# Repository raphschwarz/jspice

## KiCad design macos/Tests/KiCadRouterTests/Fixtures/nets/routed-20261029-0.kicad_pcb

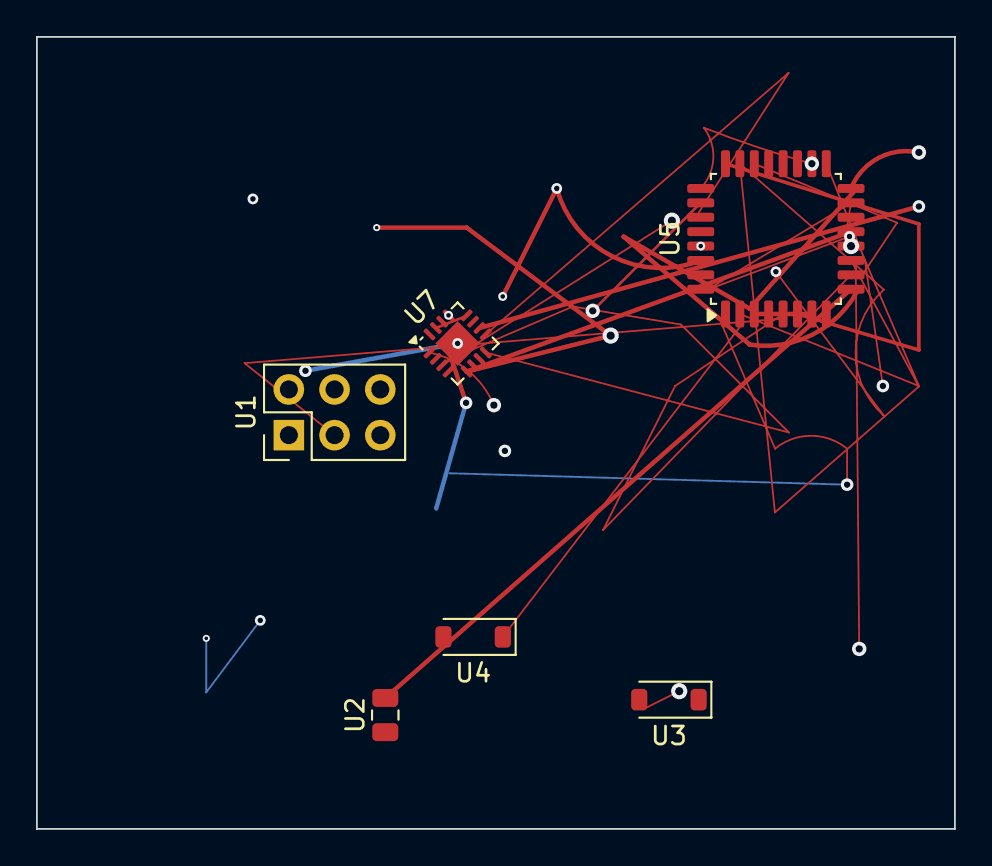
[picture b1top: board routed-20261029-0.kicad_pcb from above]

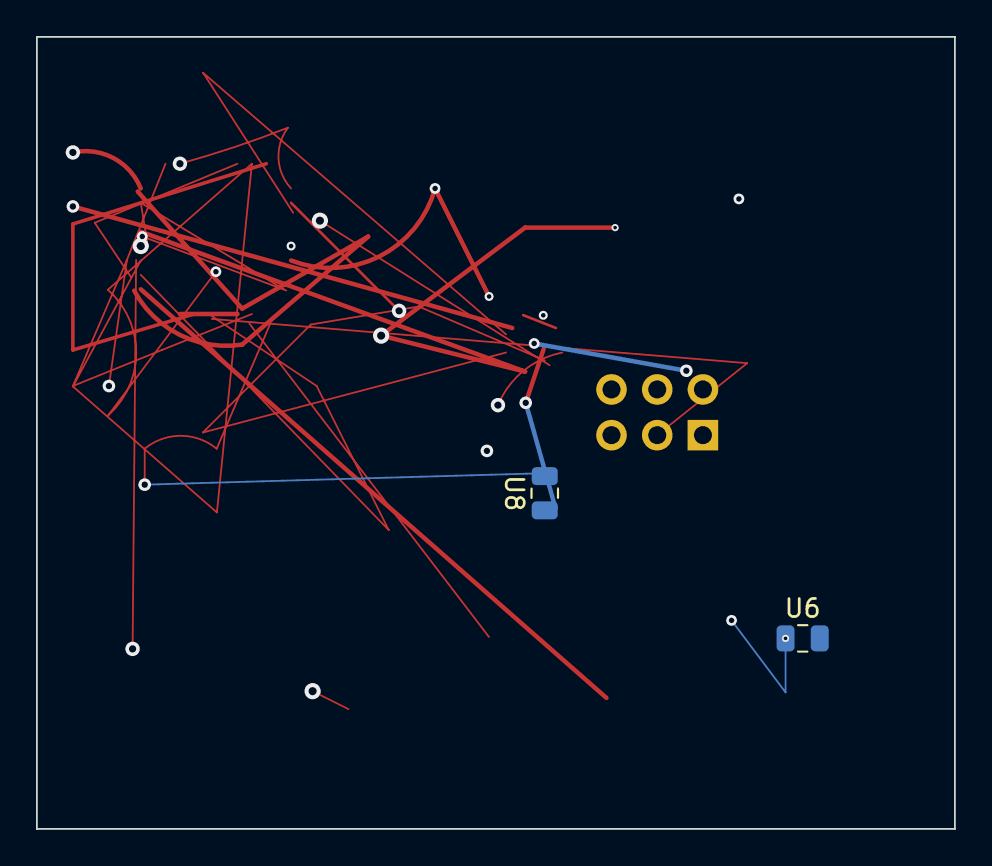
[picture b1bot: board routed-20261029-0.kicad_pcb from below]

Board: 6 copper layers, 51.0 x 44.0 mm, 8 parts (2 on the bottom side), 10 nets.

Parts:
U1: PinHeader_2x03_P2.54mm_Vertical
U2, U6, U8: C_0805_2012Metric
U3, U4: D_SOD-123
U5: LQFP-32_7x7mm_P0.8mm
U7: QFN-16-1EP_3x3mm_P0.5mm_EP1.75x1.75mm

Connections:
4k7: U5.3, U5.7, U5.30, U7.2, U7.16
+3V3: U1.1, U1.5, U5.12, U5.15, U5.32, U7.3, U7.8
/sub/CLK2: U5.6, U5.24, U5.31
/sub/clk: U5.26, U5.29, U7.12, U7.15
D12: U4.1, U5.2, U5.17, U5.18, U5.25
unnamed: U3.1, U5.1, U8.2
R1: U2.2, U5.9, U5.16, U7.10
R10: U3.2, U5.11, U5.23, U6.1, U7.1
SIG10: U1.3, U5.5, U5.10, U5.22, U5.27, U7.9
VCC: U5.13, U7.5, U7.13, U7.17, U8.1

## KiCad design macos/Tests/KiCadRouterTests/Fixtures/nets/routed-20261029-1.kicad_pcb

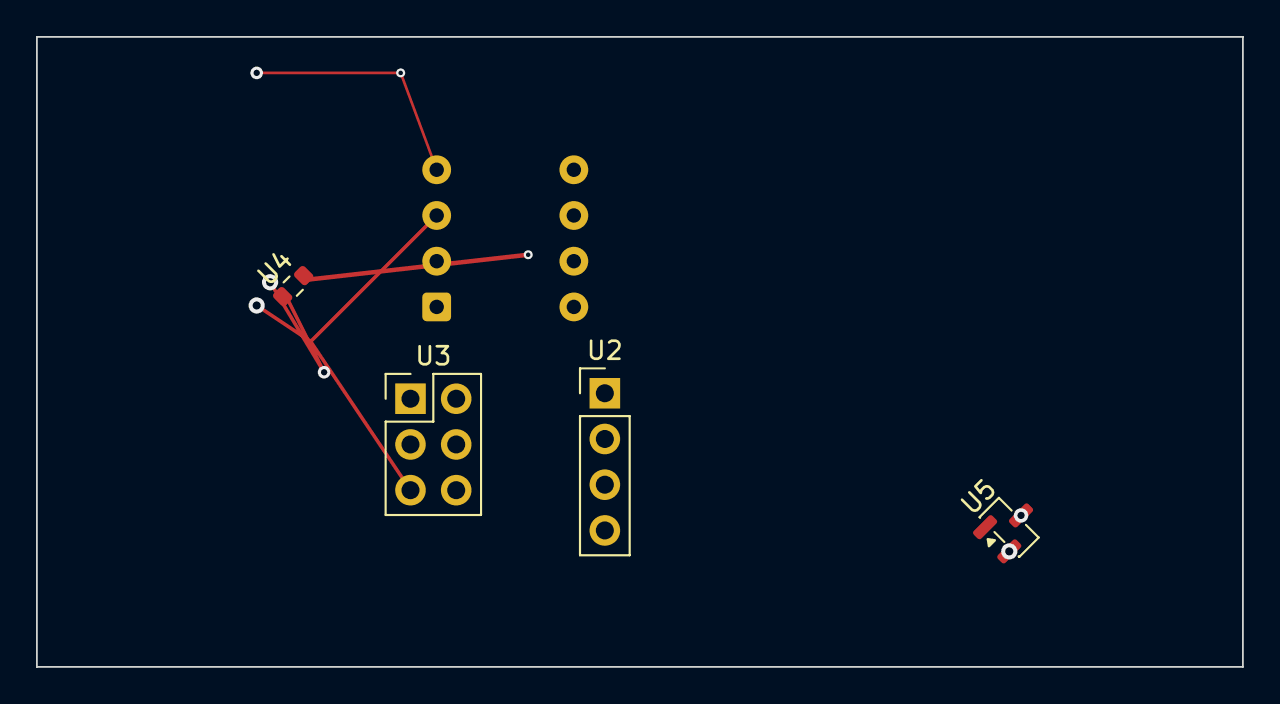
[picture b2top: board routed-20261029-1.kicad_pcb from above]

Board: 6 copper layers, 67.0 x 35.0 mm, 5 parts (1 on the bottom side), 4 nets.

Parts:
U1: DIP-8_W7.62mm
U2: PinHeader_1x04_P2.54mm_Vertical
U3: PinHeader_2x03_P2.54mm_Vertical
U4: R_0603_1608Metric
U5: SOT-23

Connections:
4K7_IN: U1.4, U1.7, U2.3
D12: U1.1, U1.8
GND: U1.3, U3.5, U5.3
VCC: U4.1, U5.2

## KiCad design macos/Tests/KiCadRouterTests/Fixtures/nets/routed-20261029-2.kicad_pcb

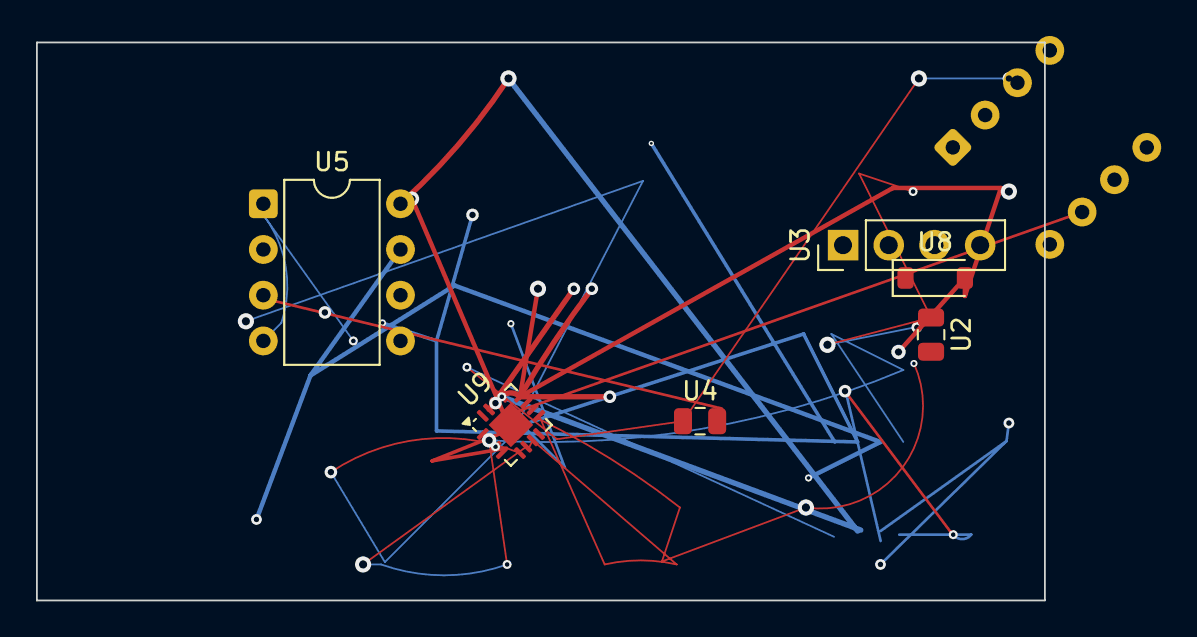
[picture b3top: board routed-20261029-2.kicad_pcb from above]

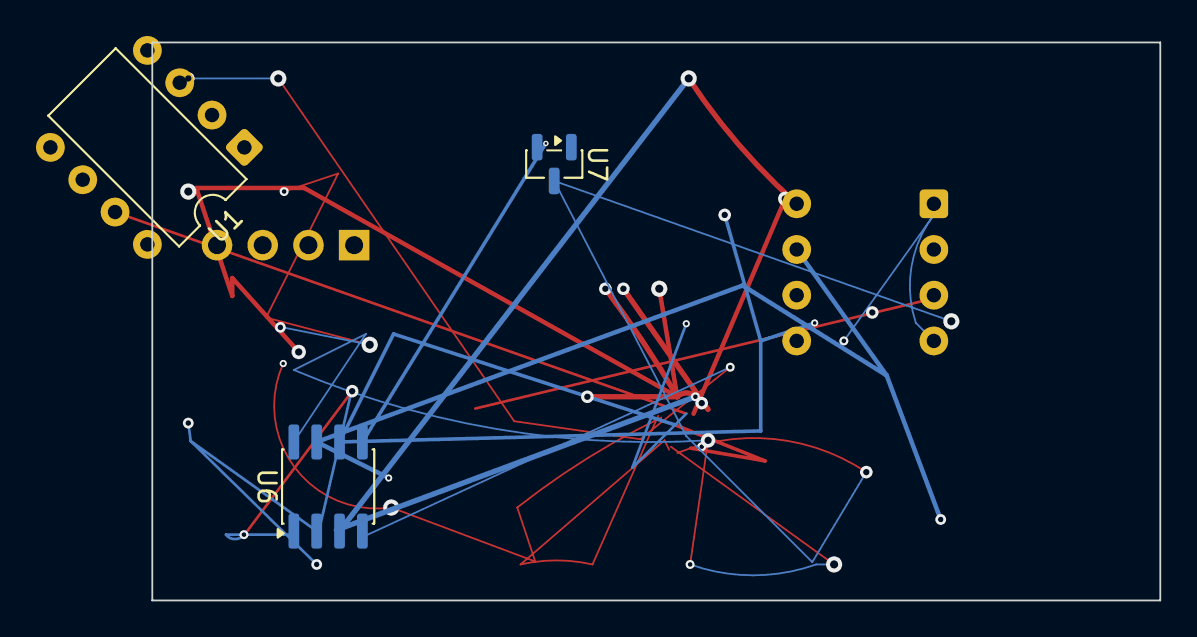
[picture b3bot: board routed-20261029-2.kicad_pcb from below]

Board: 4 copper layers, 56.0 x 31.0 mm, 9 parts (3 on the bottom side), 8 nets.

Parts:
U1, U5: DIP-8_W7.62mm
U2, U4: C_0805_2012Metric
U3: PinHeader_1x04_P2.54mm_Vertical
U6: SOIC-8_3.9x4.9mm_P1.27mm
U7: SOT-23
U8: D_SOD-123
U9: QFN-16-1EP_3x3mm_P0.5mm_EP1.75x1.75mm

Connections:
/sub/clk: U1.8, U5.5, U6.5, U6.6, U9.4, U9.16
D7: U1.7, U9.3
GND: U1.5, U4.1, U6.4, U6.8, U9.2, U9.6, U9.7, U9.9, U9.14
PWR_5V: U2.2, U5.8, U6.3, U9.13, U9.15
R1: U1.3, U5.7, U6.7, U8.2, U9.12, U9.17
SIG10: U1.4, U1.6, U4.2, U5.3
VCC: U1.1, U2.1, U5.4, U7.3, U9.5
sig3: U6.1, U6.2

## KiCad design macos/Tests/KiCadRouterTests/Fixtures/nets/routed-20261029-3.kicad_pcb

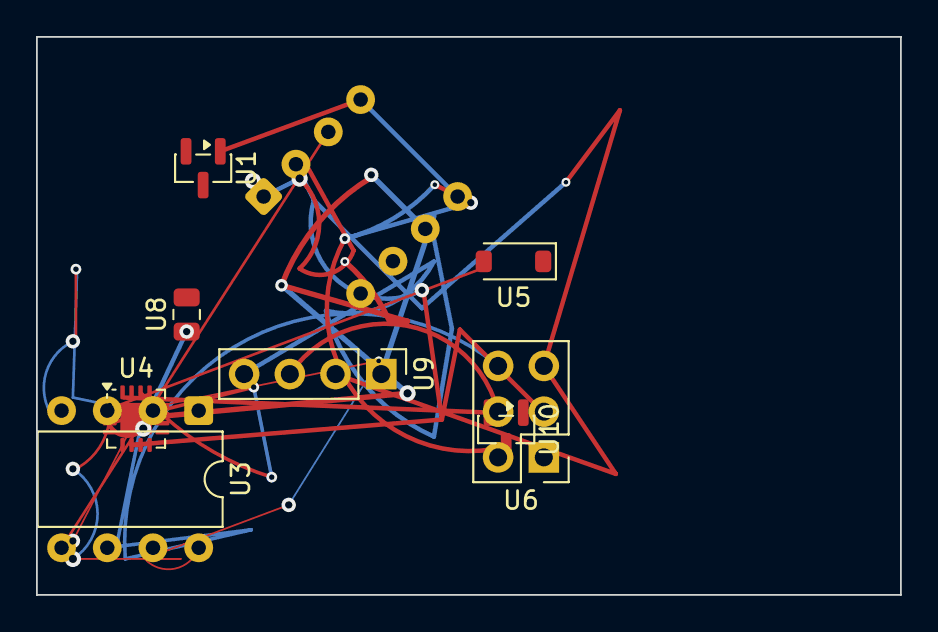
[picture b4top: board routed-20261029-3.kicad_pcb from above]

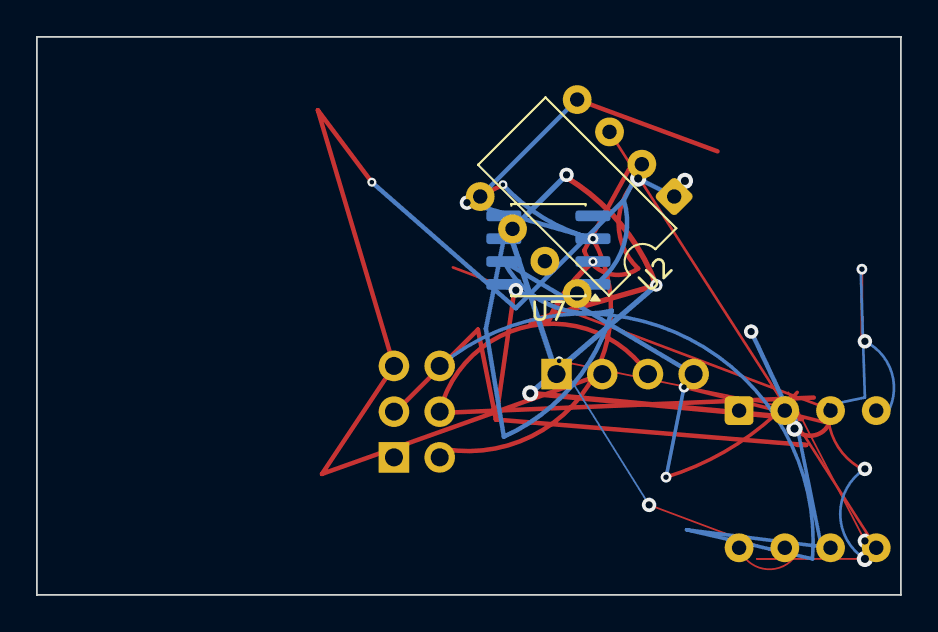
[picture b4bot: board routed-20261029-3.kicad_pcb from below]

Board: 2 copper layers, 48.0 x 31.0 mm, 10 parts (2 on the bottom side), 11 nets.

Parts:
U1, U10: SOT-23
U2, U3: DIP-8_W7.62mm
U4: QFN-16-1EP_3x3mm_P0.5mm_EP1.75x1.75mm
U5: D_SOD-123
U6: PinHeader_2x03_P2.54mm_Vertical
U7: SOIC-8_3.9x4.9mm_P1.27mm
U8: C_0805_2012Metric
U9: PinHeader_1x04_P2.54mm_Vertical

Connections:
4K7_IN: U7.6, U7.7, U9.4
/sub/CLK2: U4.3, U4.14
/sub/clk: U1.3, U2.7, U7.4, U7.5, U9.1
D7: U7.3, U10.3
D12: U2.1, U2.2, U4.6, U4.7, U6.3, U6.5, U9.2
GND: U3.8, U4.12, U4.13
N2: U1.1, U2.4, U2.5, U4.16, U6.4, U9.3
unnamed: U3.4, U4.1, U5.2, U10.1
R10: U3.2, U3.6, U6.6, U10.2
SIG10: U3.3, U8.1
VCC: U2.6, U4.17, U7.2

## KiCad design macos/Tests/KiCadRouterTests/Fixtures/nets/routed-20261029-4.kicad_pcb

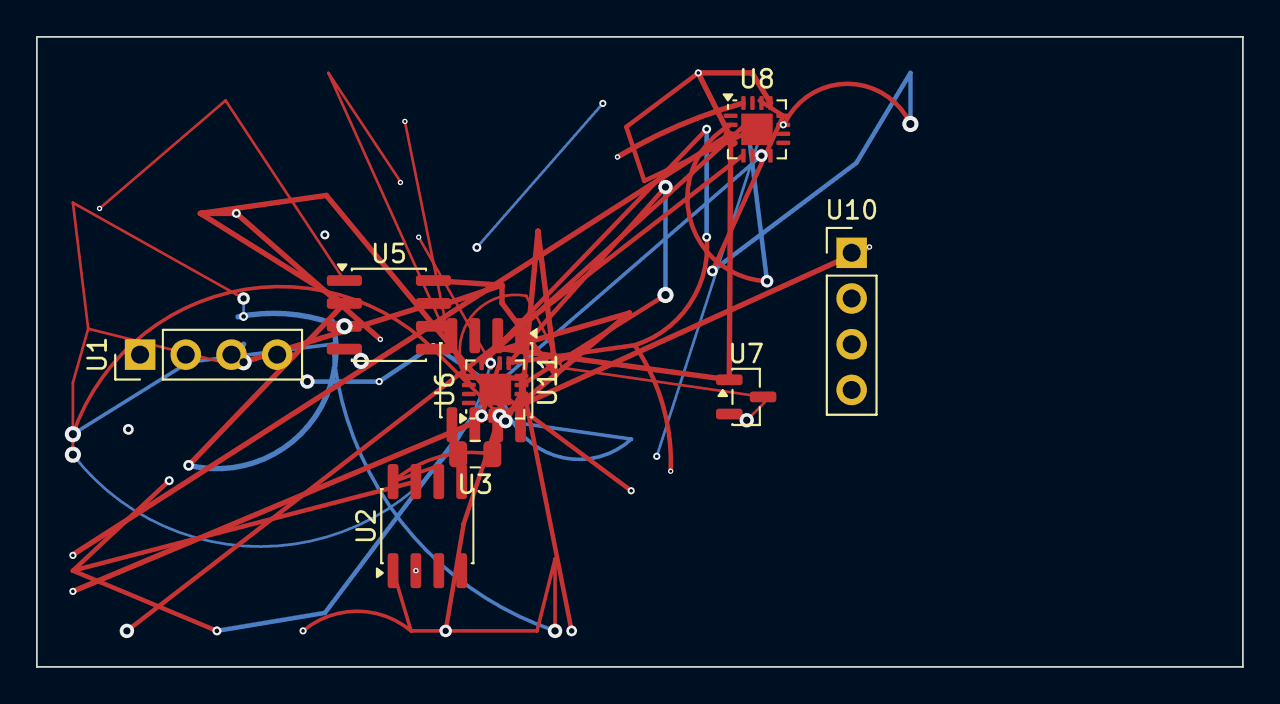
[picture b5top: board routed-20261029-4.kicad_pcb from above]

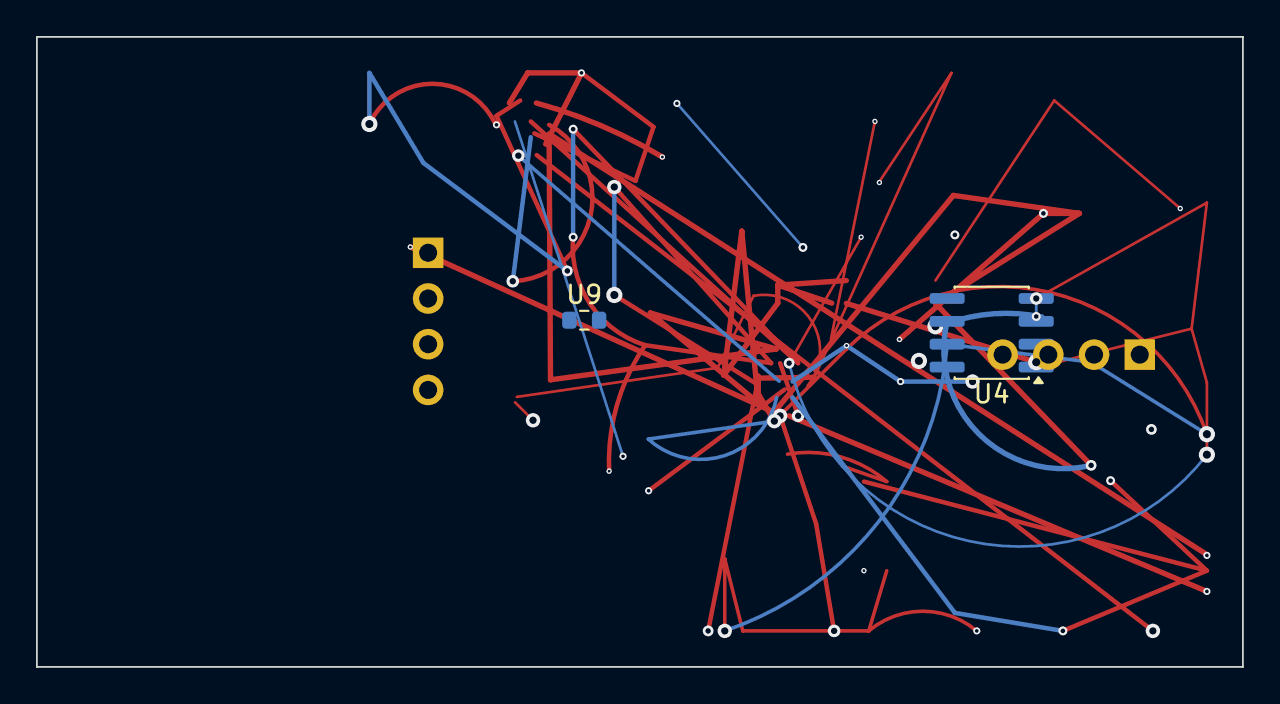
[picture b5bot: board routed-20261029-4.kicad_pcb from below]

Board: 4 copper layers, 67.0 x 35.0 mm, 11 parts (2 on the bottom side), 6 nets.

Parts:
U1, U10: PinHeader_1x04_P2.54mm_Vertical
U2, U4, U5, U11: SOIC-8_3.9x4.9mm_P1.27mm
U3: C_0805_2012Metric
U6, U8: QFN-16-1EP_3x3mm_P0.5mm_EP1.75x1.75mm
U7: SOT-23
U9: R_0603_1608Metric

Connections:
4K7_IN: U1.4, U2.7, U6.3, U6.7, U6.9, U6.12, U8.2, U8.5, U8.8, U8.11, U8.12, U8.14, U9.1, U10.3
GND: U4.3, U4.6, U5.2, U5.3, U5.6, U6.2, U6.4, U6.6, U6.8, U6.13, U6.15, U8.3, U8.6, U8.16, U11.7
unnamed: U4.2, U5.7, U5.8, U6.5, U7.1, U8.4, U8.13, U11.3
R10: U6.1, U6.10, U6.17
SIG2: U1.1, U1.3, U4.4, U5.1, U6.11, U6.14, U7.3, U11.4
sig3: U1.2, U2.1, U2.2, U2.6, U2.8, U3.1, U4.7, U5.5, U8.7, U9.2

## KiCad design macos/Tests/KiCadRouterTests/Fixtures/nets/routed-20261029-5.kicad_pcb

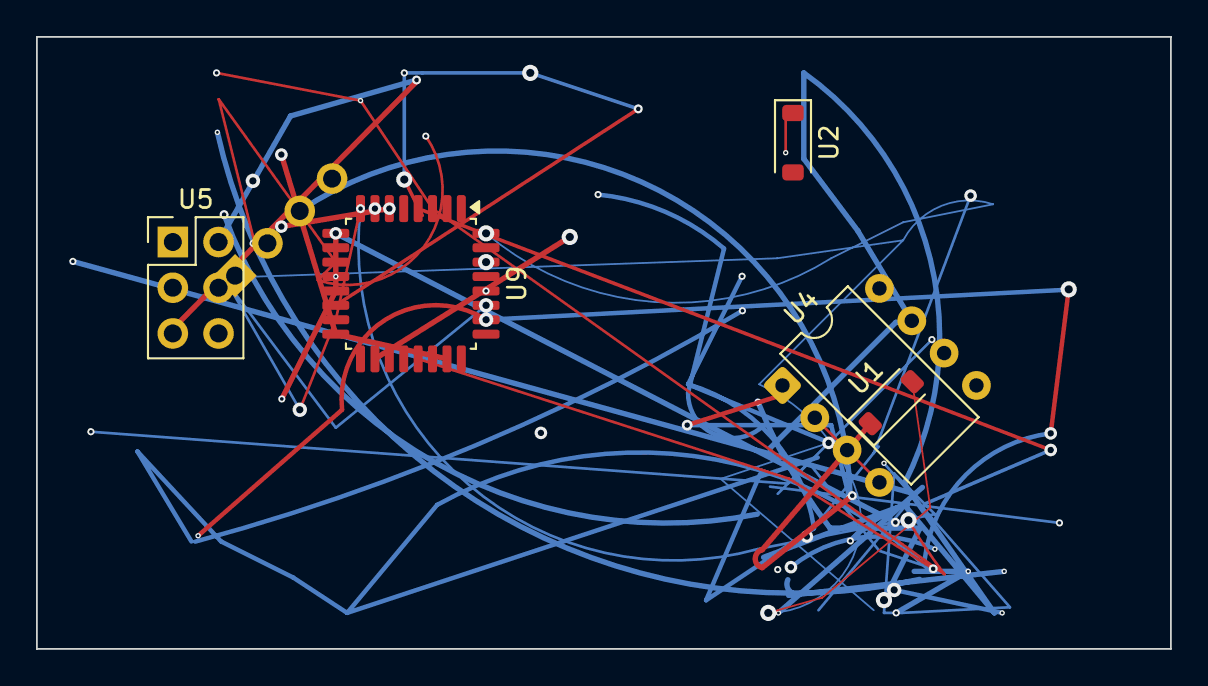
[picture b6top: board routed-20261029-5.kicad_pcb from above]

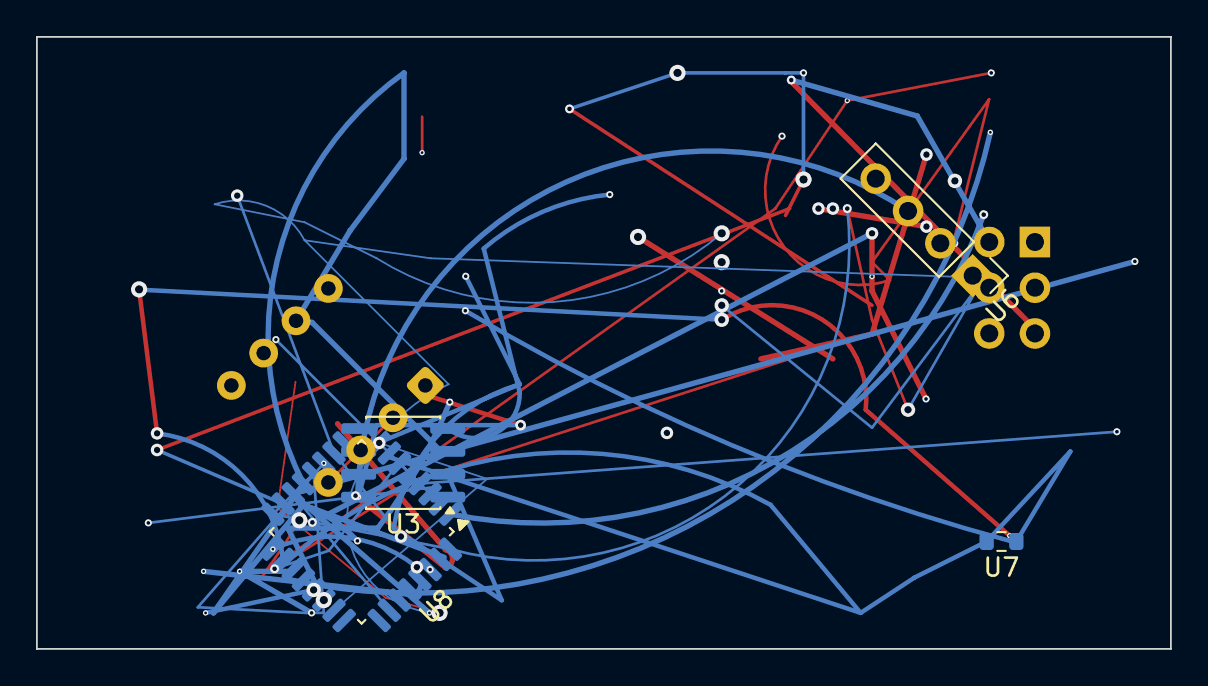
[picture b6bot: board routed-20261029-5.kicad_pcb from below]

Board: 4 copper layers, 63.0 x 34.0 mm, 9 parts (4 on the bottom side), 10 nets.

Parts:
U1, U2: D_SOD-123
U3: SOIC-8_3.9x4.9mm_P1.27mm
U4: DIP-8_W7.62mm
U5: PinHeader_2x03_P2.54mm_Vertical
U6: PinHeader_1x04_P2.54mm_Vertical
U7: R_0603_1608Metric
U8, U9: LQFP-32_7x7mm_P0.8mm

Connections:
4K7_IN: U3.3, U4.7, U8.13, U8.31
+3V3: U3.1, U3.2, U4.3, U7.1, U7.2, U8.7, U8.18, U9.26, U9.30
/sub/CLK2: U1.1, U6.3, U8.19, U8.28, U8.29, U9.9, U9.13, U9.18
/sub/clk: U4.2, U4.4, U8.3, U8.6, U9.21
D7: U3.4, U3.8, U4.1, U8.17, U8.21, U8.30, U9.10, U9.20
GND: U8.15, U9.4, U9.7, U9.12, U9.14
N2: U2.1, U4.5, U5.4, U8.4, U8.10, U8.11, U8.12, U8.16, U8.32, U9.8, U9.15, U9.27
PWR_5V: U1.2, U3.7, U6.1, U8.8, U8.23, U9.1, U9.32
R1: U5.3, U8.20, U8.26, U9.3, U9.11, U9.28
R10: U5.2, U5.5, U5.6, U6.4, U8.1, U8.14, U8.22, U9.6, U9.16, U9.23

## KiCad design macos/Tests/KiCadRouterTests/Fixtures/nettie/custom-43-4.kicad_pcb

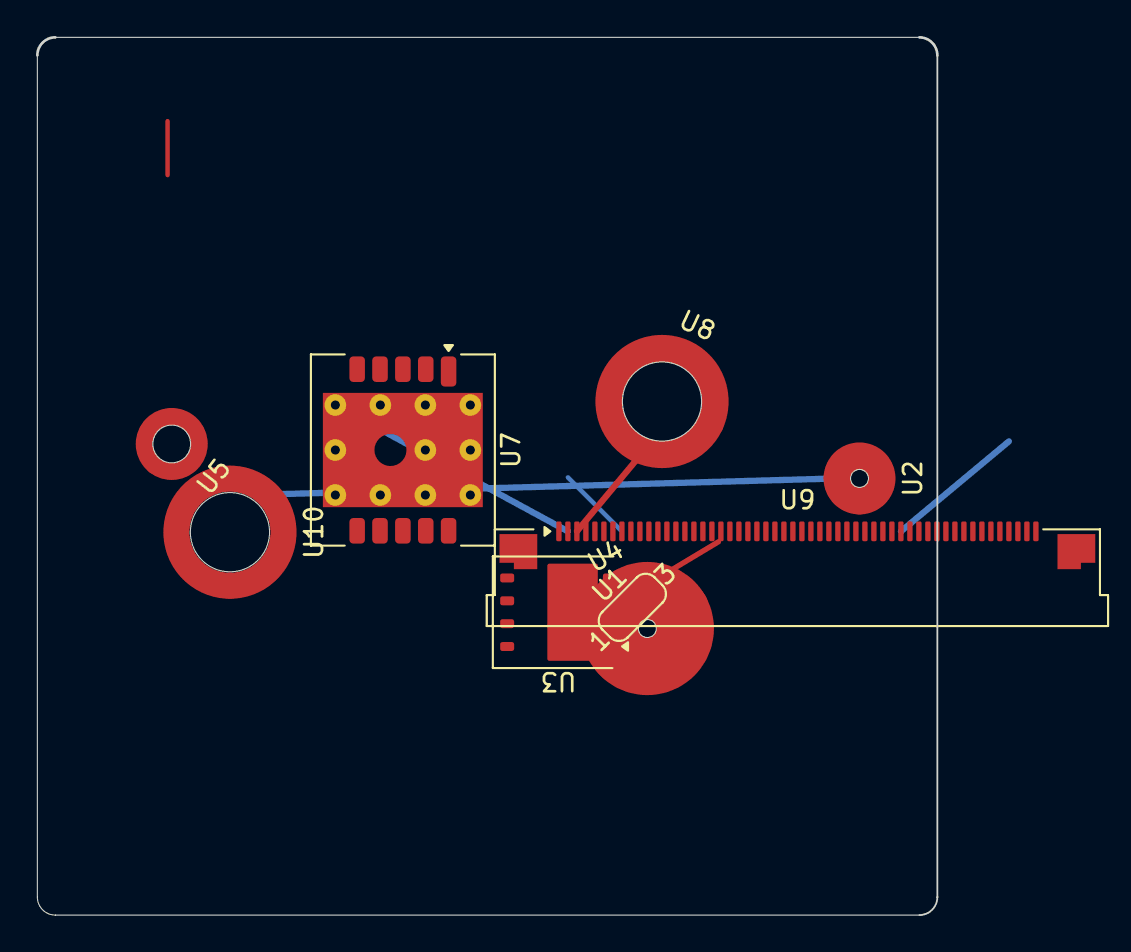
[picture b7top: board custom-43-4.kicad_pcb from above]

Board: 2 copper layers, 50.0 x 48.8 mm, 10 parts (1 on the bottom side), 6 nets.

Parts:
U1: SolderJumper-3_P1.3mm_Bridged12_RoundedPad1.0x1.5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; SolderJumper-3_P1.3mm_Bridged12_RoundedPad1.0x1.5mm_NumberL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
U2: Mounting_Wuerth_WA-SMSI-M1.6_H3.5mm_ThreadDepth2m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; Mounting_Wuerth_WA-SMSI-M1.6_H3.5mm_ThreadDepth2mm_97730356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
U3: ST_PowerFLAT_HV-8_5x6mm
U4: Mounting_Wuerth_WA-SMSE-ExternalM3_H12mm_97711203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; Mounting_Wuerth_WA-SMSE-ExternalM3_H12mm_9771120360
U5: Mounting_Wuerth_WA-SMSI-M1.6_H1mm_9774010633
U6: QFN-32-1EP_4x4mm_P0.4mm_EP2.65x2.65mm
U7: OriginGPS_ORG1510
U8: Mounting_Wuerth_WA-SMSI-M3_H12mm_9774120360
U9: Amphenol_F32Q-1A7x1-11054_1x54-1MP_P0.5mm_Horizon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; Amphenol_F32Q-1A7x1-11054_1x54-1MP_P0.5mm_Horizontal
U10: Mounting_Wuerth_WA-SMSR-3.2mm_H10.6mm_ReverseMoun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; Mounting_Wuerth_WA-SMSR-3.2mm_H10.6mm_ReverseMount_97751069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

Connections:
/sub/clk: U2.1, U3.4, U3.8, U5.1, U6.8, U6.27, U7.5, U7.7, U7.9, U7.11, U9.6, U9.7, U9.15, U9.18, U9.32, U9.37, U10.1
D7: U4.1, U6.1, U6.12, U6.17, U6.25, U7.6, U8.1, U9.3, U9.11, U9.13, U9.25, U9.42, U9.45
GND: U5.1, U6.7, U6.9, U6.10, U6.16, U6.18, U6.19, U6.20, U6.31, U7.2, U7.3, U7.4, U7.10, U7.11, U8.1, U9.12, U9.22, U9.29, U9.31, U9.38, U9.41, U9.43, U9.MP
N2: U1.2, U2.1, U3.6, U3.7, U5.1, U6.6, U6.29, U7.8, U9.17, U9.21, U9.26, U9.30, U9.34, U9.36, U9.44, U9.49, U9.50, U9.54, U10.1
N3: U1.1, U1.3, U3.2, U4.1, U5.1, U6.2, U6.5, U6.13, U6.26, U7.11, U9.2, U9.4, U9.8, U9.27, U9.33, U9.48, U9.51, U9.53, U10.1
SIG2: U3.3, U6.11, U6.15, U6.23, U7.11, U9.5, U9.24, U9.28, U9.39, U9.40, U9.46
